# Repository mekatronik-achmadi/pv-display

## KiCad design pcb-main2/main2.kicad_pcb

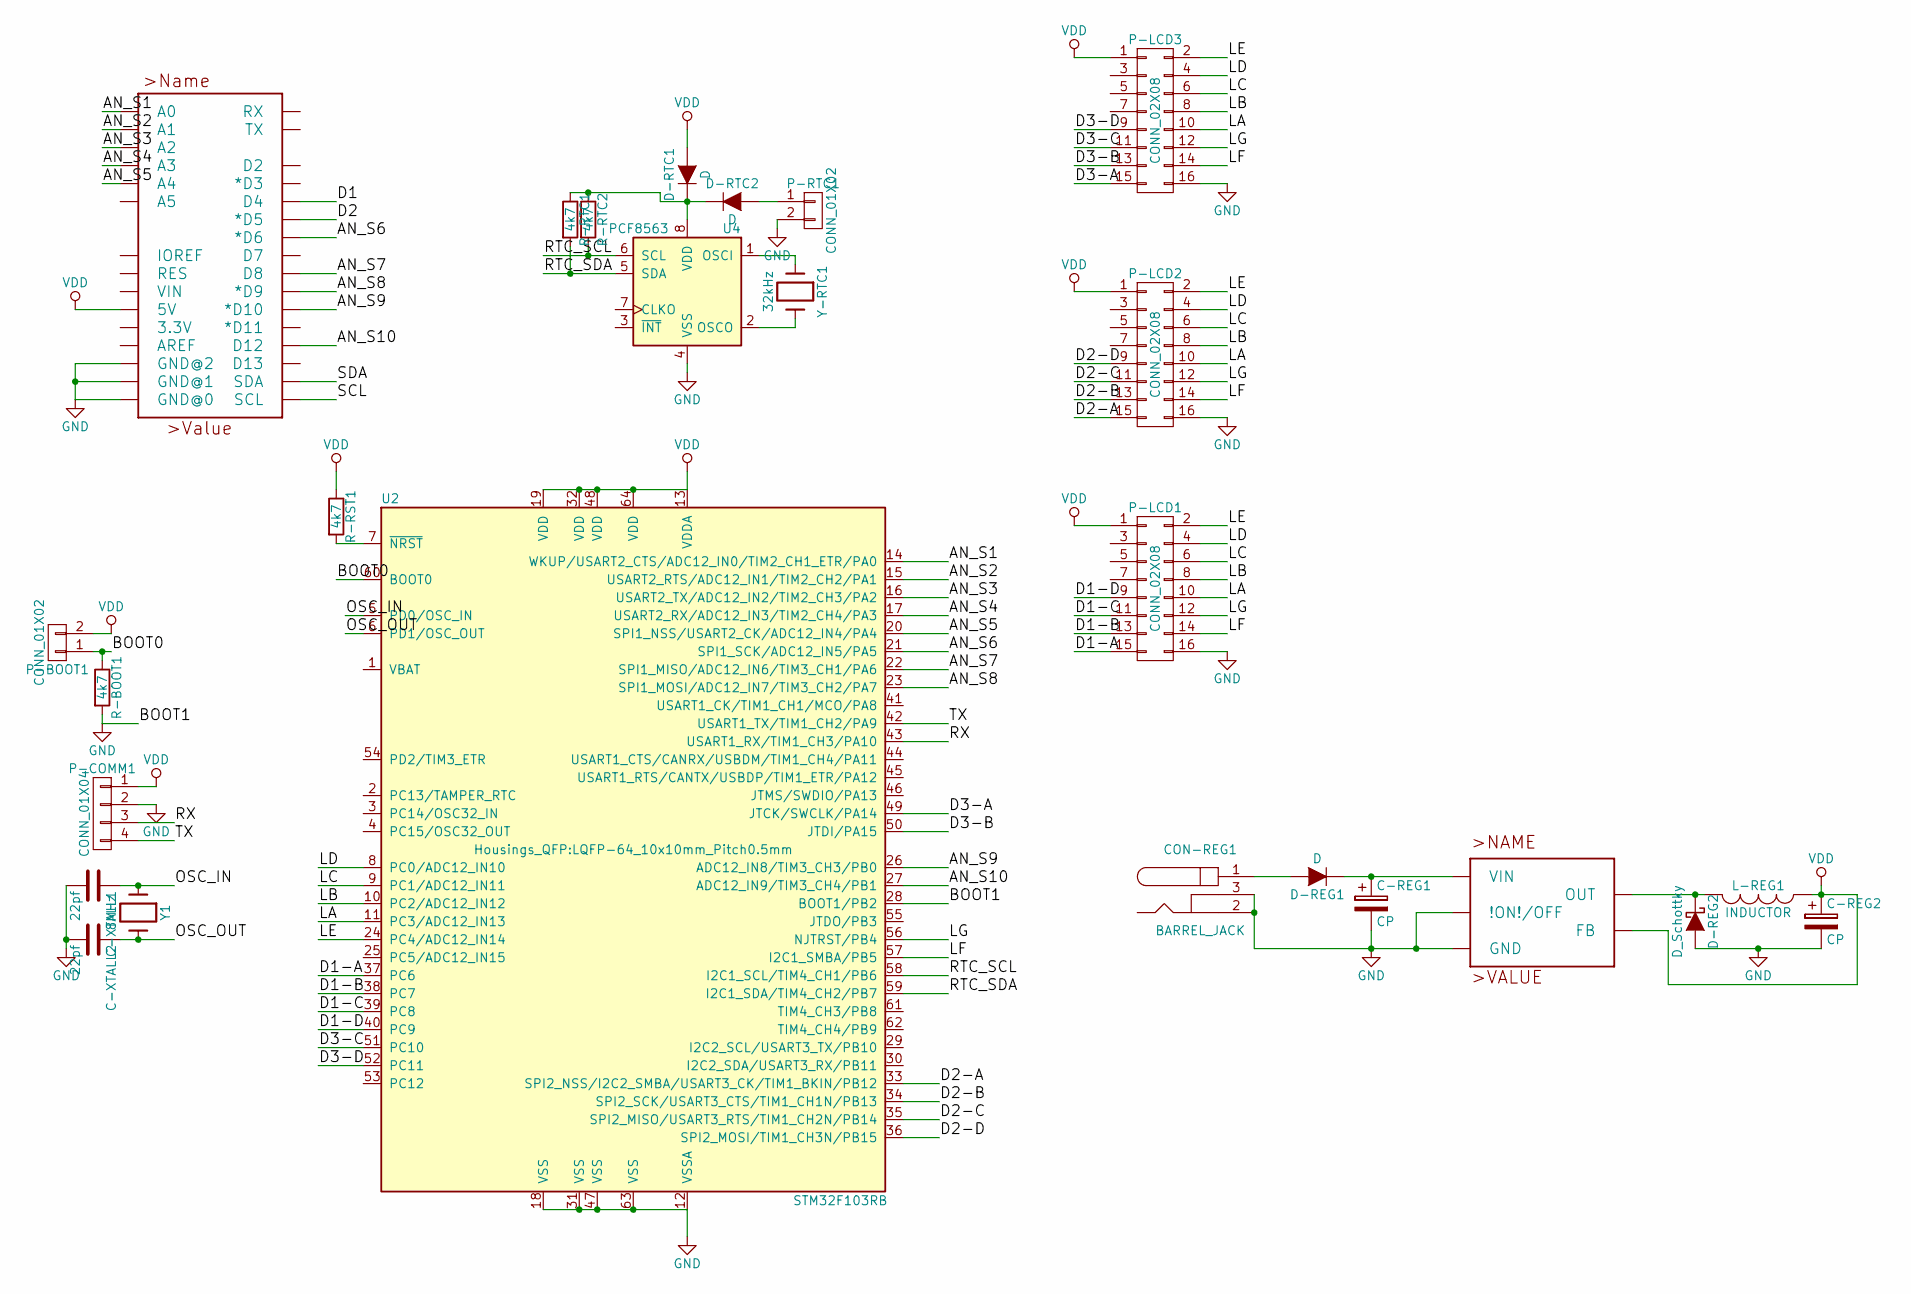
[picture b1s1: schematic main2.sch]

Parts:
C-REG1, C-REG2: CP; C_Radial_D5_L6_P2.5
C-XTALL1, C-XTALL2: 22pf; C_1206_HandSoldering
CON-REG1: BARREL_JACK
D-REG1: D; SMA_Handsoldering
D-REG2: D_Schottky; SMA_Handsoldering
D-RTC1, D-RTC2: D; SMA_Handsoldering
L-REG1: INDUCTOR; INDUCTOR_V
P-BOOT1: CONN_01X02; Pin_Header_Straight_1x02
P-COMM1: CONN_01X04; Pin_Header_Straight_1x04
P-LCD1, P-LCD2, P-LCD3: CONN_02X08; Pin_Header_Straight_2x08
P-RTC1: CONN_01X02; Pin_Header_Straight_1x02
R-BOOT1: 4k7; R_1206_HandSoldering
R-RST1: 4k7; R_1206_HandSoldering
R-RTC1, R-RTC2: 4k7; C_1206_HandSoldering
U1: ARDUINO_R3_SHIELD_UNO_R3_SHIELD; UNO_R3_SHIELD
U2: STM32F103RB; LQFP-64_10x10mm_Pitch0.5mm
U3: LM2596S_TO263-3; TO-263-5Lead
U4: PCF8563; SOIJ-8_5.3x5.3mm_Pitch1.27mm
Y1: 8MHz; HC-49V
Y-RTC1: 32kHz; Crystal_Watch

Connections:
/AN_S1: U1.A0, U2.14 (WKUP/USART2_CTS/ADC12_IN0/TIM2_CH1_ETR/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)
/AN_S2: U1.A1, U2.15 (USART2_RTS/ADC12_IN1/TIM2_CH2/PA1)
/AN_S3: U1.A2, U2.16 (USART2_TX/ADC12_IN2/TIM2_CH3/PA2)
/AN_S4: U1.A3, U2.17 (USART2_RX/ADC12_IN3/TIM2_CH4/PA3)
/AN_S5: U1.A4, U2.20 (SPI1_NSS/USART2_CK/ADC12_IN4/PA4)
/AN_S6: U1.D6 (*D6), U2.21 (SPI1_SCK/ADC12_IN5/PA5)
/AN_S7: U1.D8, U2.22 (SPI1_MISO/ADC12_IN6/TIM3_CH1/PA6)
/AN_S8: U1.D9 (*D9), U2.23 (SPI1_MOSI/ADC12_IN7/TIM3_CH2/PA7)
/AN_S9: U1.D10 (*D10), U2.26 (ADC12_IN8/TIM3_CH3/PB0)
/AN_S10: U1.D12, U2.27 (ADC12_IN9/TIM3_CH4/PB1)
/BOOT0: P-BOOT1.1, R-BOOT1.1, U2.60 (BOOT0)
/D1: U1.D4
/D1-A: P-LCD1.15, U2.37 (PC6)
/D1-B: P-LCD1.13, U2.38 (PC7)
/D1-C: P-LCD1.11, U2.39 (PC8)
/D1-D: P-LCD1.9, U2.40 (PC9)
/D2: U1.D5 (*D5)
/D2-A: P-LCD2.15, U2.33 (SPI2_NSS/I2C2_SMBA/USART3_CK/TIM1_BKIN/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)
/D2-B: P-LCD2.13, U2.34 (SPI2_SCK/USART3_CTS/TIM1_CH1N/PB13)
/D2-C: P-LCD2.11, U2.35 (SPI2_MISO/USART3_RTS/TIM1_CH2N/PB14)
/D2-D: P-LCD2.9, U2.36 (SPI2_MOSI/TIM1_CH3N/PB15)
/D3-A: P-LCD3.15, U2.49 (JTCK/SWCLK/PA14)
/D3-B: P-LCD3.13, U2.50 (JTDI/PA15)
/D3-C: P-LCD3.11, U2.51 (PC10)
/D3-D: P-LCD3.9, U2.52 (PC11)
/LA: P-LCD1.10, P-LCD2.10, P-LCD3.10, U2.11 (PC3/ADC12_IN13)
/LB: P-LCD1.8, P-LCD2.8, P-LCD3.8, U2.10 (PC2/ADC12_IN12)
/LC: P-LCD1.6, P-LCD2.6, P-LCD3.6, U2.9 (PC1/ADC12_IN11)
/LD: P-LCD1.4, P-LCD2.4, P-LCD3.4, U2.8 (PC0/ADC12_IN10)
/LE: P-LCD1.2, P-LCD2.2, P-LCD3.2, U2.24 (PC4/ADC12_IN14)
/LF: P-LCD1.14, P-LCD2.14, P-LCD3.14, U2.57 (I2C1_SMBA/PB5)
/LG: P-LCD1.12, P-LCD2.12, P-LCD3.12, U2.56 (NJTRST/PB4)
/OSC_IN: C-XTALL1.1, U2.5 (PD0/OSC_IN), Y1.1
/OSC_OUT: C-XTALL2.1, U2.6 (PD1/OSC_OUT), Y1.2
/RTC_SCL: R-RTC2.2, U2.58 (I2C1_SCL/TIM4_CH1/PB6), U4.6 (SCL)
/RTC_SDA: R-RTC1.2, U2.59 (I2C1_SDA/TIM4_CH2/PB7), U4.5 (SDA)
/RX: P-COMM1.3, U2.43 (USART1_RX/TIM1_CH3/PA10)
/SCL: U1.SCL
/SDA: U1.SDA
/TX: P-COMM1.4, U2.42 (USART1_TX/TIM1_CH2/PA9)
GND: C-REG1.2, C-REG2.2, C-XTALL1.2, C-XTALL2.2, CON-REG1.2, CON-REG1.3, D-REG2.2 (A), P-COMM1.2, P-LCD1.16, P-LCD2.16, P-LCD3.16, P-RTC1.2, R-BOOT1.2, U1.GND@ (GND@0), U2.12 (VSSA), U2.18 (VSS), U2.28 (BOOT1/PB2), U2.31 (VSS), U2.47 (VSS), U2.63 (VSS), U3.3 (GND), U3.5 (!ON!/OFF), U4.4 (VSS)
unnamed: C-REG1.1, D-REG1.1 (K), U3.1 (VIN)
unnamed: CON-REG1.1, D-REG1.2 (A)
unnamed: D-REG2.1 (K), L-REG1.2, U3.2 (OUT)
unnamed: D-RTC1.1 (K), D-RTC2.1 (K), R-RTC1.1, R-RTC2.1, U4.8 (VDD)
unnamed: D-RTC2.2 (A), P-RTC1.1
unnamed: R-RST1.2, U2.7 (~NRST)
unnamed: U4.1 (OSCI), Y-RTC1.1
unnamed: U4.2 (OSCO), Y-RTC1.2
VDD: C-REG2.1, D-RTC1.2 (A), L-REG1.1, P-BOOT1.2, P-COMM1.1, P-LCD1.1, P-LCD2.1, P-LCD3.1, R-RST1.1, U1.5V, U2.13 (VDDA), U2.19 (VDD), U2.32 (VDD), U2.48 (VDD), U2.64 (VDD), U3.4 (FB)

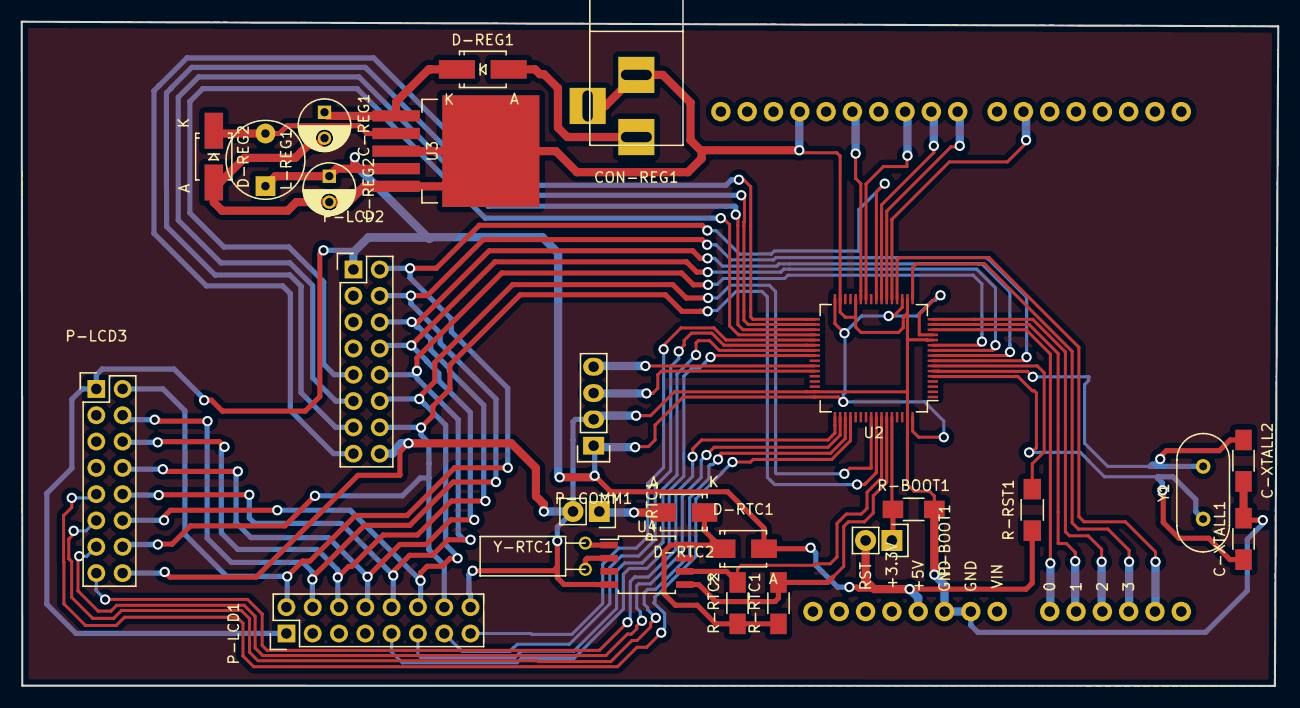
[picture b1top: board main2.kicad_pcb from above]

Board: 2 copper layers, 121.3 x 64.1 mm, 26 parts (0 on the bottom side), 46 nets.

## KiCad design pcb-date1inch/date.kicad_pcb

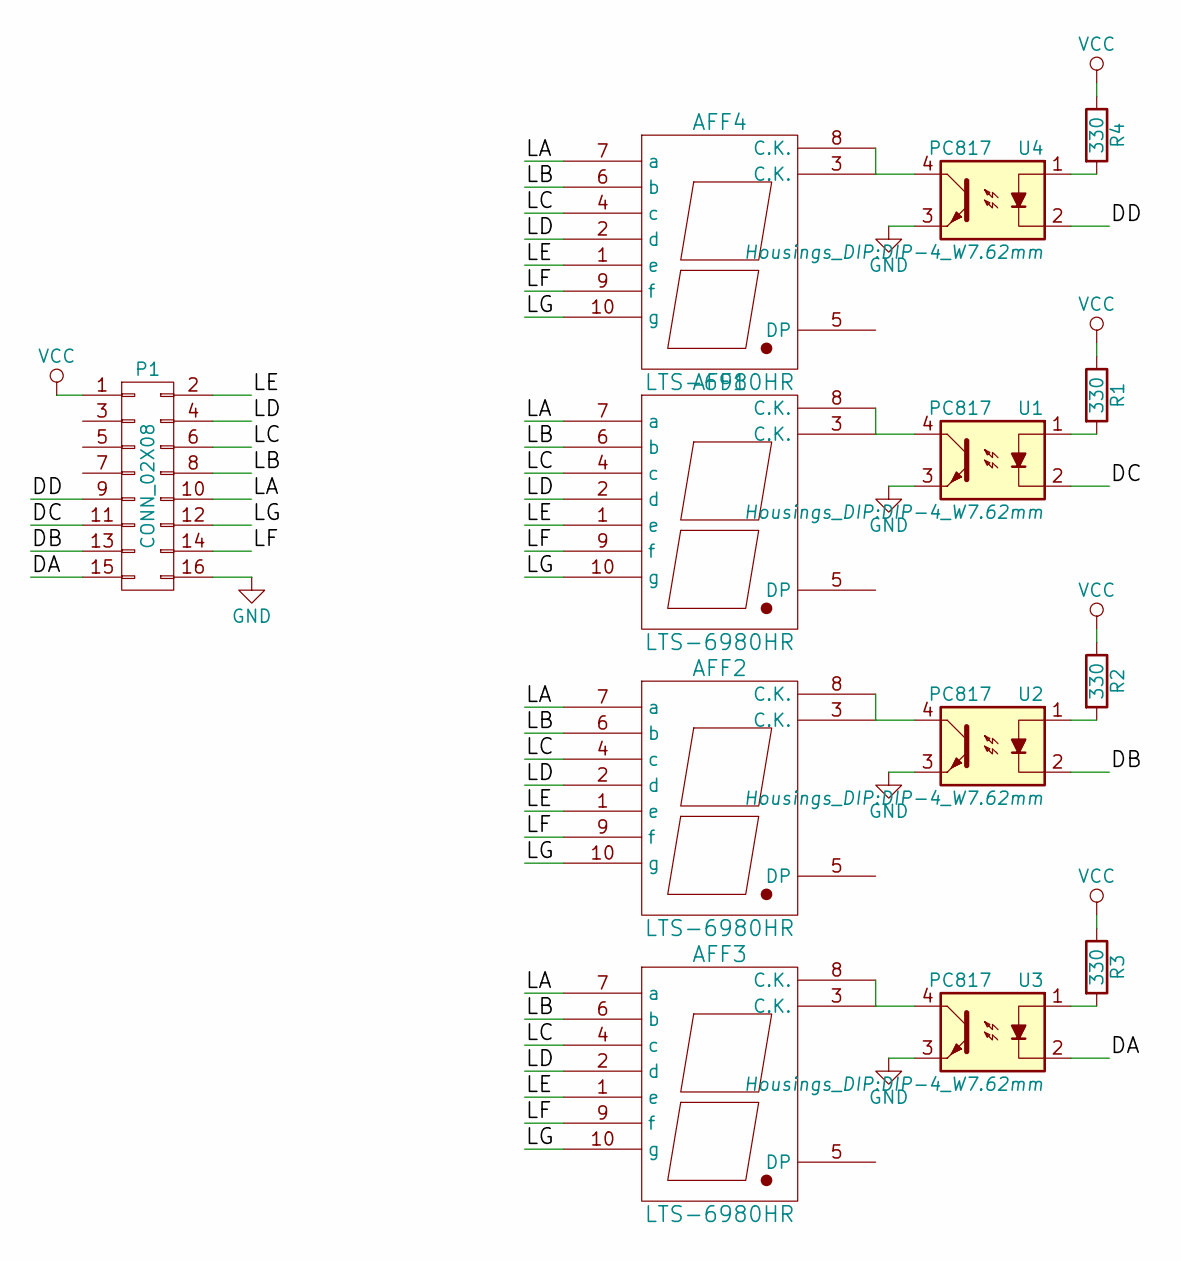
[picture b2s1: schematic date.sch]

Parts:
AFF1, AFF2, AFF3, AFF4: LTS-6980HR; 7SegmentLED_LTS6760_LTS6780
P1: CONN_02X08; Pin_Header_Straight_2x08
R1, R2, R3, R4: 330; Resistor_Horizontal_RM10mm
U1, U2, U3, U4: PC817; DIP-4_W7.62mm

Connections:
/DA: P1.15, U3.2
/DB: P1.13, U2.2
/DC: P1.11, U1.2
/DD: P1.9, U4.2
/LA: AFF1.7 (a), AFF2.7 (a), AFF3.7 (a), AFF4.7 (a), P1.10
/LB: AFF1.6 (b), AFF2.6 (b), AFF3.6 (b), AFF4.6 (b), P1.8
/LC: AFF1.4 (c), AFF2.4 (c), AFF3.4 (c), AFF4.4 (c), P1.6
/LD: AFF1.2 (d), AFF2.2 (d), AFF3.2 (d), AFF4.2 (d), P1.4
/LE: AFF1.1 (e), AFF2.1 (e), AFF3.1 (e), AFF4.1 (e), P1.2
/LF: AFF1.9 (f), AFF2.9 (f), AFF3.9 (f), AFF4.9 (f), P1.14
/LG: AFF1.10 (g), AFF2.10 (g), AFF3.10 (g), AFF4.10 (g), P1.12
GND: P1.16, U1.3, U2.3, U3.3, U4.3
unnamed: AFF1.3 (C.K.), AFF1.8 (C.K.), U1.4
unnamed: AFF2.3 (C.K.), AFF2.8 (C.K.), U2.4
unnamed: AFF3.3 (C.K.), AFF3.8 (C.K.), U3.4
unnamed: AFF4.3 (C.K.), AFF4.8 (C.K.), U4.4
unnamed: R1.2, U1.1
unnamed: R2.2, U2.1
unnamed: R3.2, U3.1
unnamed: R4.2, U4.1
VCC: P1.1, R1.1, R2.1, R3.1, R4.1

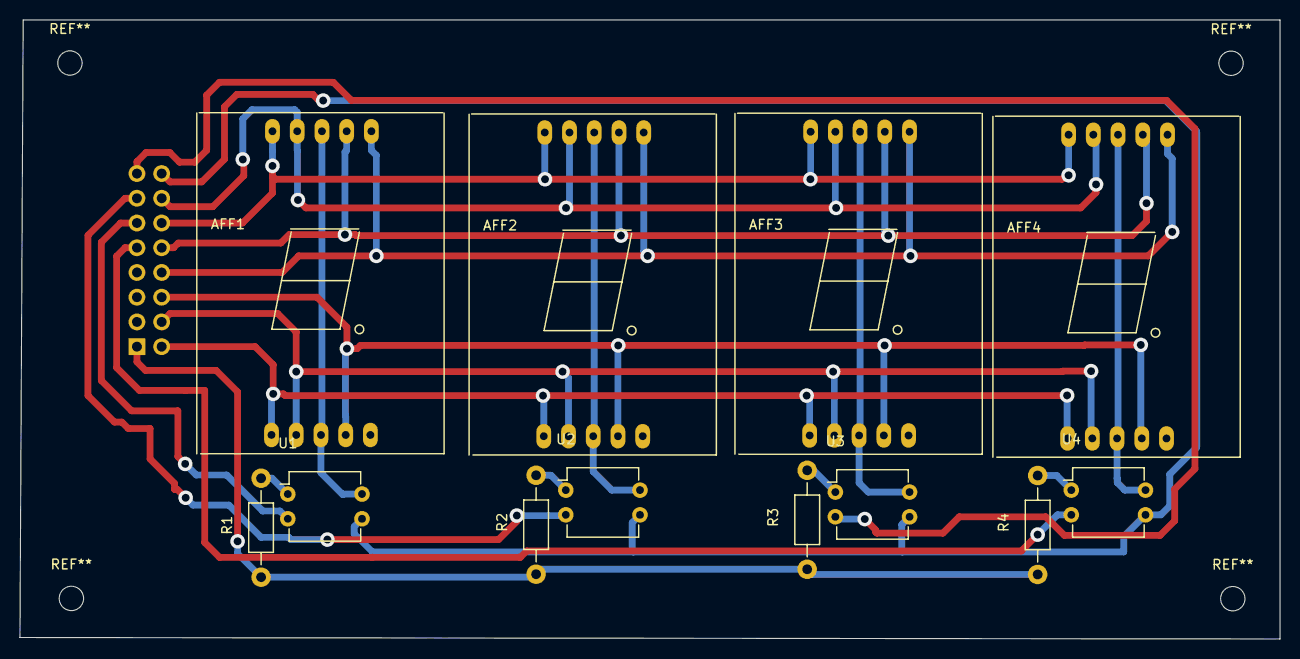
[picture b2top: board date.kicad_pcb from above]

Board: 2 copper layers, 129.4 x 63.6 mm, 13 parts (1 on the bottom side), 21 nets.

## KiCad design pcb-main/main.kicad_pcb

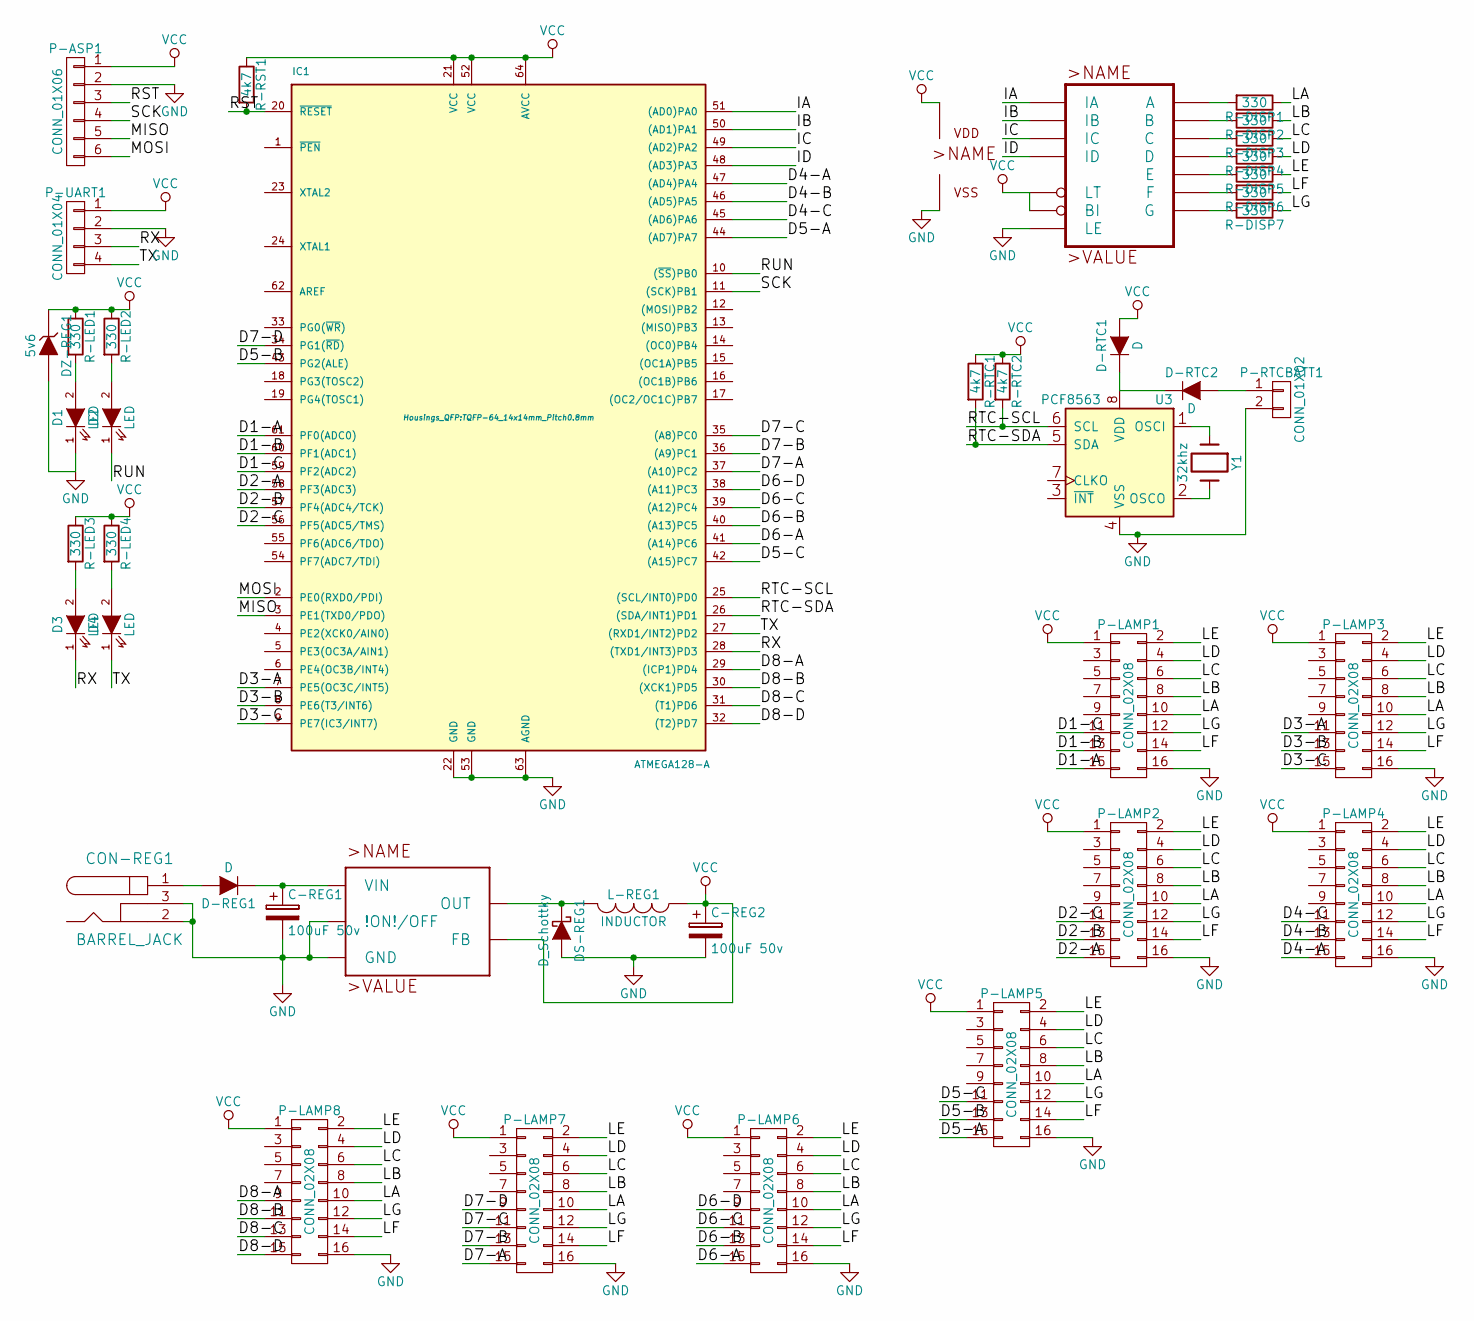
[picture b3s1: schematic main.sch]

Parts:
C-REG1, C-REG2: 100uF 50v; C_Radial_D5_L6_P2.5
CON-REG1: BARREL_JACK; JACK_ALIM
D1, D2, D3, D4: LED; LED-3MM
D-REG1: D; Diode_DO-35_SOD27_Horizontal_RM10
D-RTC1, D-RTC2: D; Diode_DO-35_SOD27_Horizontal_RM10
DS-REG1: D_Schottky; Diode_DO-35_SOD27_Horizontal_RM10
DZ-REG1: 5v6; Diode_DO-35_SOD27_Horizontal_RM10
IC1: ATMEGA128-A; TQFP-64_14x14mm_Pitch0.8mm
L-REG1: INDUCTOR; INDUCTOR_V
P-ASP1: CONN_01X06; Pin_Header_Straight_1x06
P-LAMP1, P-LAMP2, P-LAMP3, P-LAMP4, P-LAMP5, P-LAMP6, P-LAMP7, P-LAMP8: CONN_02X08; Pin_Header_Straight_2x08
P-RTCBATT1: CONN_01X02; Pin_Header_Straight_1x02
P-UART1: CONN_01X04; Pin_Header_Straight_1x04
R-DISP1, R-DISP2, R-DISP3, R-DISP4, R-DISP5, R-DISP6, R-DISP7: 330; Resistor_Horizontal_RM10mm
R-LED1, R-LED2, R-LED3, R-LED4: 330; Resistor_Horizontal_RM10mm
R-RST1: 4k7; Resistor_Horizontal_RM10mm
R-RTC1, R-RTC2: 4k7; Resistor_Horizontal_RM10mm
U1: 4511N_DIL16; DIP-16_W7.62mm_LongPads
U2: LM2596S_TO263-5; TO-263-5Lead
U3: PCF8563; SOIJ-8_5.3x5.3mm_Pitch1.27mm
Y1: 32khz; Crystal_Watch

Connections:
/D1-A: IC1.61 (PF0(ADC0)), P-LAMP1.15
/D1-B: IC1.60 (PF1(ADC1)), P-LAMP1.13
/D1-C: IC1.59 (PF2(ADC2)), P-LAMP1.11
/D2-A: IC1.58 (PF3(ADC3)), P-LAMP2.15
/D2-B: IC1.57 (PF4(ADC4/TCK)), P-LAMP2.13
/D2-C: IC1.56 (PF5(ADC5/TMS)), P-LAMP2.11
/D3-A: IC1.7 (PE5(OC3C/INT5)), P-LAMP3.11
/D3-B: IC1.8 (PE6(T3/INT6)), P-LAMP3.13
/D3-C: IC1.9 (PE7(IC3/INT7)), P-LAMP3.15
/D4-A: IC1.47 ((AD4)PA4), P-LAMP4.15
/D4-B: IC1.46 ((AD5)PA5), P-LAMP4.13
/D4-C: IC1.45 ((AD6)PA6), P-LAMP4.11
/D5-A: IC1.44 ((AD7)PA7), P-LAMP5.15
/D5-B: IC1.43 (PG2(ALE)), P-LAMP5.13
/D5-C: IC1.42 ((A15)PC7), P-LAMP5.11
/D6-A: IC1.41 ((A14)PC6), P-LAMP6.15
/D6-B: IC1.40 ((A13)PC5), P-LAMP6.13
/D6-C: IC1.39 ((A12)PC4), P-LAMP6.11
/D6-D: IC1.38 ((A11)PC3), P-LAMP6.9
/D7-A: IC1.37 ((A10)PC2), P-LAMP7.15
/D7-B: IC1.36 ((A9)PC1), P-LAMP7.13
/D7-C: IC1.35 ((A8)PC0), P-LAMP7.11
/D7-D: IC1.34 (PG1(~RD~)), P-LAMP7.9
/D8-A: IC1.29 ((ICP1)PD4), P-LAMP8.9
/D8-B: IC1.30 ((XCK1)PD5), P-LAMP8.11
/D8-C: IC1.31 ((T1)PD6), P-LAMP8.13
/D8-D: IC1.32 ((T2)PD7), P-LAMP8.15
/IA: IC1.51 ((AD0)PA0), U1.7 (IA)
/IB: IC1.50 ((AD1)PA1), U1.1 (IB)
/IC: IC1.49 ((AD2)PA2), U1.2 (IC)
/ID: IC1.48 ((AD3)PA3), U1.6 (ID)
/LA: P-LAMP1.10, P-LAMP2.10, P-LAMP3.10, P-LAMP4.10, P-LAMP5.10, P-LAMP6.10, P-LAMP7.10, P-LAMP8.10, R-DISP1.1
/LB: P-LAMP1.8, P-LAMP2.8, P-LAMP3.8, P-LAMP4.8, P-LAMP5.8, P-LAMP6.8, P-LAMP7.8, P-LAMP8.8, R-DISP2.1
/LC: P-LAMP1.6, P-LAMP2.6, P-LAMP3.6, P-LAMP4.6, P-LAMP5.6, P-LAMP6.6, P-LAMP7.6, P-LAMP8.6, R-DISP3.1
/LD: P-LAMP1.4, P-LAMP2.4, P-LAMP3.4, P-LAMP4.4, P-LAMP5.4, P-LAMP6.4, P-LAMP7.4, P-LAMP8.4, R-DISP4.1
/LE: P-LAMP1.2, P-LAMP2.2, P-LAMP3.2, P-LAMP4.2, P-LAMP5.2, P-LAMP6.2, P-LAMP7.2, P-LAMP8.2, R-DISP5.1
/LF: P-LAMP1.14, P-LAMP2.14, P-LAMP3.14, P-LAMP4.14, P-LAMP5.14, P-LAMP6.14, P-LAMP7.14, P-LAMP8.14, R-DISP6.1
/LG: P-LAMP1.12, P-LAMP2.12, P-LAMP3.12, P-LAMP4.12, P-LAMP5.12, P-LAMP6.12, P-LAMP7.12, P-LAMP8.12, R-DISP7.1
/MISO: IC1.3 (PE1(TXD0/PDO)), P-ASP1.5
/MOSI: IC1.2 (PE0(RXD0/PDI)), P-ASP1.6
/RST: IC1.20 (~RESET), P-ASP1.3, R-RST1.2
/RTC-SCL: IC1.25 ((SCL/INT0)PD0), R-RTC2.2, U3.6 (SCL)
/RTC-SDA: IC1.26 ((SDA/INT1)PD1), R-RTC1.2, U3.5 (SDA)
/RUN: D2.1 (K), IC1.10 ((~SS~)PB0)
/RX: D3.1 (K), IC1.28 ((TXD1/INT3)PD3), P-UART1.3
/SCK: IC1.11 ((SCK)PB1), P-ASP1.4
/TX: D4.1 (K), IC1.27 ((RXD1/INT2)PD2), P-UART1.4
GND: C-REG1.2, C-REG2.2, CON-REG1.2, CON-REG1.3, D1.1 (K), DS-REG1.2 (A), DZ-REG1.2 (A), IC1.22 (GND), IC1.53 (GND), IC1.63 (AGND), P-ASP1.2, P-LAMP1.16, P-LAMP2.16, P-LAMP3.16, P-LAMP4.16, P-LAMP5.16, P-LAMP6.16, P-LAMP7.16, P-LAMP8.16, P-RTCBATT1.2, P-UART1.2, U1.5 (LE), U1.8 (VSS), U2.3 (GND), U2.5 (!ON!/OFF), U3.4 (VSS)
unnamed: C-REG1.1, D-REG1.1 (K), U2.1 (VIN)
unnamed: CON-REG1.1, D-REG1.2 (A)
unnamed: D1.2 (A), R-LED1.2
unnamed: D2.2 (A), R-LED2.2
unnamed: D3.2 (A), R-LED3.2
unnamed: D4.2 (A), R-LED4.2
unnamed: D-RTC1.1 (K), D-RTC2.1 (K), U3.8 (VDD)
unnamed: D-RTC2.2 (A), P-RTCBATT1.1
unnamed: DS-REG1.1 (K), L-REG1.2, U2.2 (OUT)
unnamed: R-DISP1.2, U1.13 (A)
unnamed: R-DISP2.2, U1.12 (B)
unnamed: R-DISP3.2, U1.11 (C)
unnamed: R-DISP4.2, U1.10 (D)
unnamed: R-DISP5.2, U1.9 (E)
unnamed: R-DISP6.2, U1.15 (F)
unnamed: R-DISP7.2, U1.14 (G)
unnamed: U3.1 (OSCI), Y1.1
unnamed: U3.2 (OSCO), Y1.2
VCC: C-REG2.1, D-RTC1.2 (A), DZ-REG1.1 (K), IC1.21 (VCC), IC1.52 (VCC), IC1.64 (AVCC), L-REG1.1, P-ASP1.1, P-LAMP1.1, P-LAMP2.1, P-LAMP3.1, P-LAMP4.1, P-LAMP5.1, P-LAMP6.1, P-LAMP7.1, P-LAMP8.1, P-UART1.1, R-LED1.1, R-LED2.1, R-LED3.1, R-LED4.1, R-RST1.1, R-RTC1.1, R-RTC2.1, U1.3 (LT), U1.4 (BI), U1.16 (VDD), U2.4 (FB)

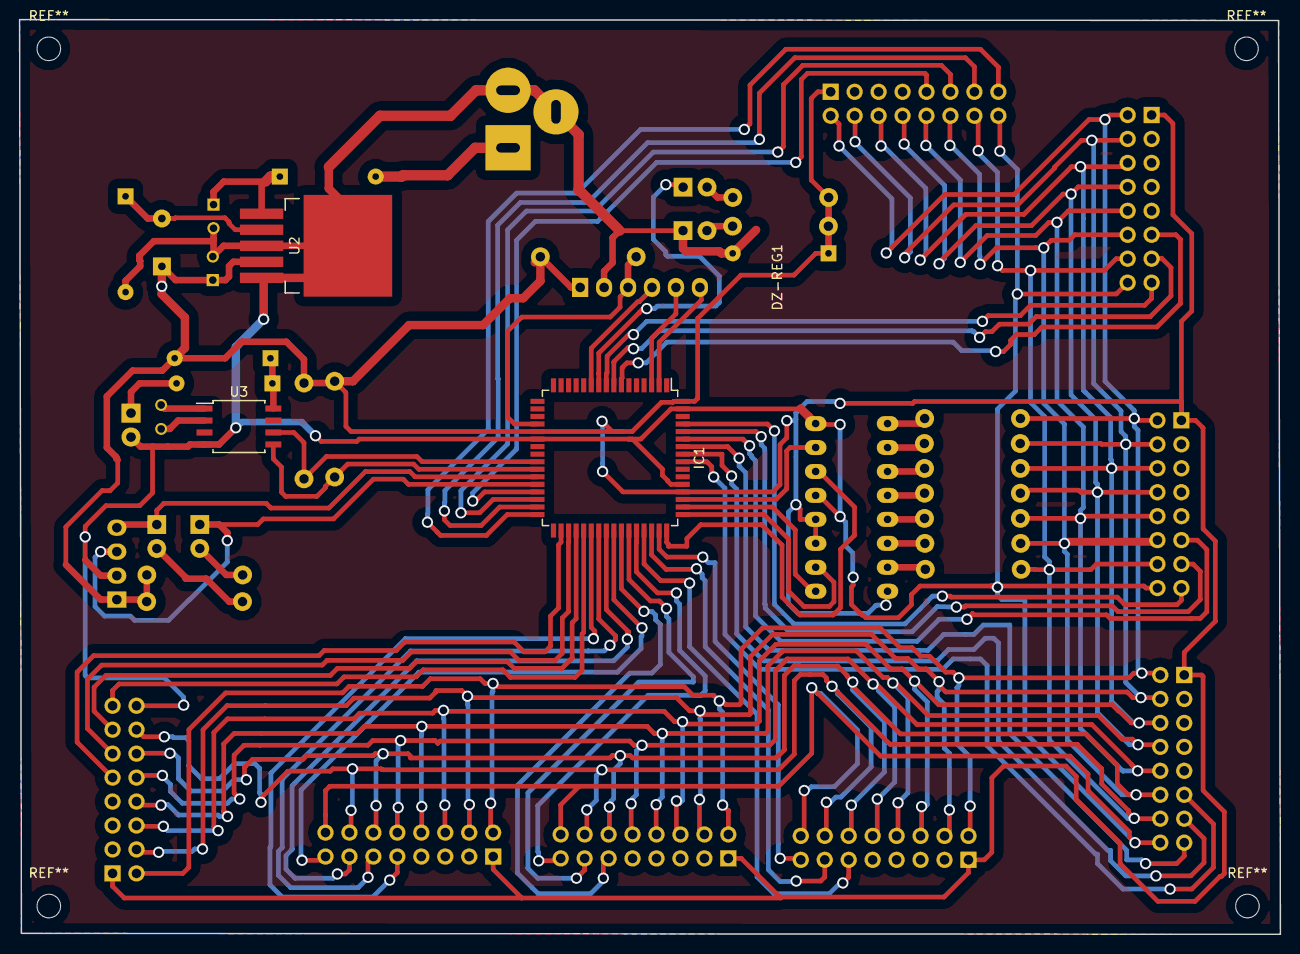
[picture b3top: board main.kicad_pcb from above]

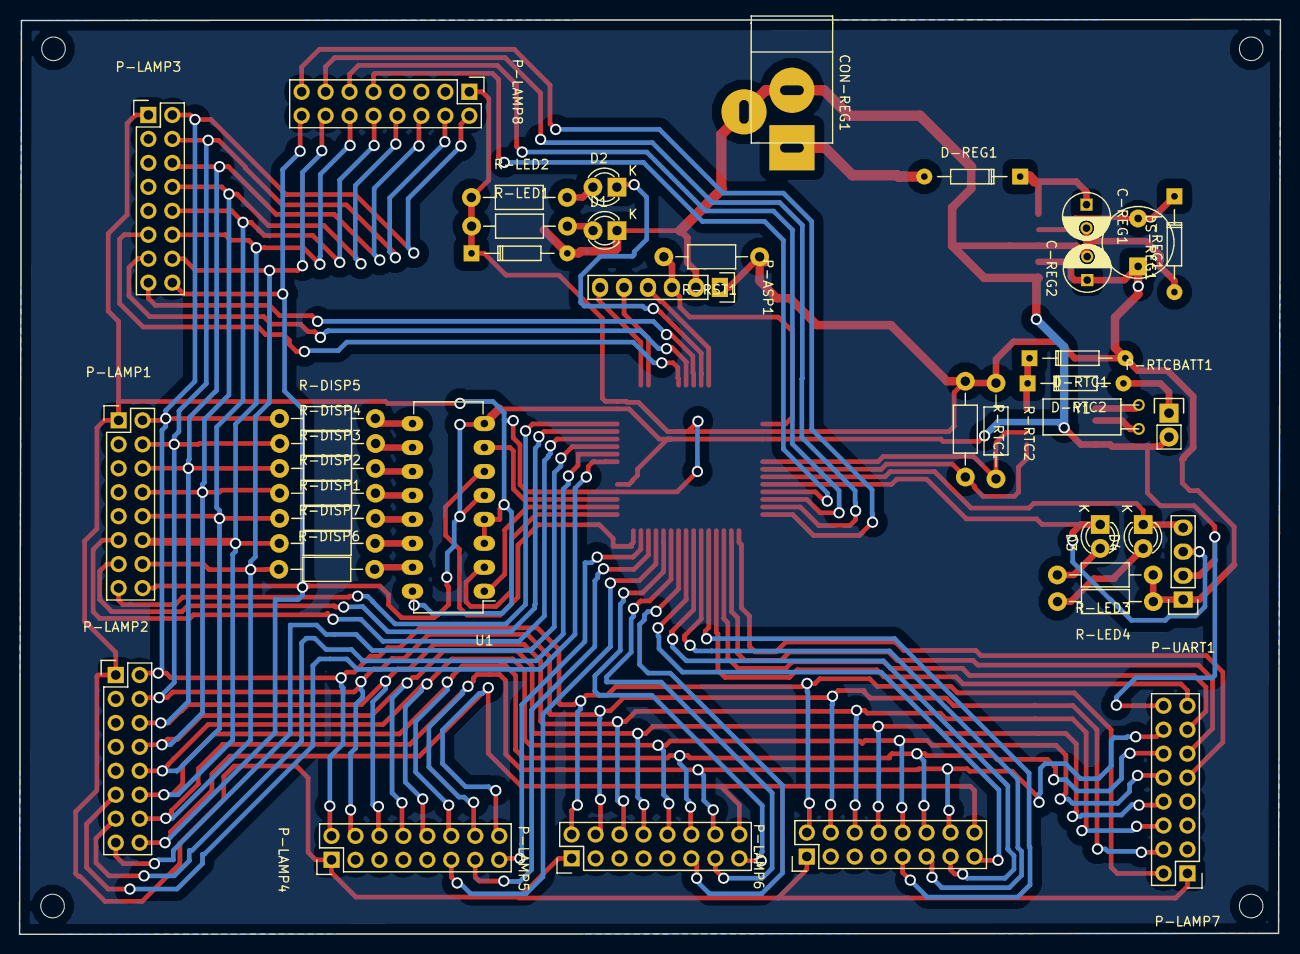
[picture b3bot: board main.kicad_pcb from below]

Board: 2 copper layers, 133.7 x 97.0 mm, 43 parts (40 on the bottom side), 67 nets.

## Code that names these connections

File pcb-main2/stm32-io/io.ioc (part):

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Mcu.Name=STM32F103R(8-B)Tx
Mcu.Package=LQFP64
PA0-WKUP.Mode=IN0
PA0-WKUP.Signal=ADC1_IN0
PA1.Mode=IN1
PA1.Signal=ADC1_IN1
PA10.Mode=Asynchronous
PA10.Signal=USART1_RX
PA2.Mode=IN2
PA2.Signal=ADC1_IN2
PA3.Mode=IN3
PA3.Signal=ADC1_IN3
PA4.Mode=IN4
PA4.Signal=ADC1_IN4
PA5.Mode=IN5
PA5.Signal=ADC1_IN5
PA6.Mode=IN6
PA6.Signal=ADC1_IN6
PA7.Mode=IN7
PA7.Signal=ADC1_IN7
PA9.Mode=Asynchronous
PA9.Signal=USART1_TX
PB0.Mode=IN8
PB0.Signal=ADC1_IN8
PB1.Mode=IN9
PB1.Signal=ADC1_IN9
PB10.Signal=GPIO_Output
PB2.Mode=Event-Out
PB2.Signal=CORTEX_EVENT_OUT
PB6.Mode=I2C
PB6.Signal=I2C1_SCL
PB7.Mode=I2C
PB7.Signal=I2C1_SDA
PC0.Signal=GPIO_Output
PC1.Signal=GPIO_Output
PC2.Signal=GPIO_Output
PC3.Signal=GPIO_Output
PC4.Signal=GPIO_Output
PC5.Signal=GPIO_Output

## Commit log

2016-05-15 1 inch date board
2016-08-12 development
2016-08-22 finish
